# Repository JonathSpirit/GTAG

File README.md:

# GTAG

Copyright (C) 2020 Guillaume Guillet\
Licensed under CERN OHL v.1.2

<table border="0px">
<tr>
<td>
This documentation describes Open Hardware and is licensed under the CERN OHL v. 1.2.
</td>
</tr>
<tr>
<td>
You may redistribute and modify this documentation under the terms of the
CERN OHL v.1.2. (http://ohwr.org/cernohl). This documentation is distributed
WITHOUT ANY EXPRESS OR IMPLIED WARRANTY, INCLUDING OF
MERCHANTABILITY, SATISFACTORY QUALITY AND FITNESS FOR A
PARTICULAR PURPOSE. Please see the CERN OHL v.1.2 for applicable
conditions
</td>
</tr>
</table>

## Description
GTAG is a small adaptation card for the silicon-labs JTAG Debug adapter.
The utility is to not having to place the big 1x05 header connector and not solder any resistance for
small board conception.

Silicon-labs USB-Debug-Adapter : https://www.silabs.com/documents/public/user-guides/8-bit-USB-Debug-Adapter.pdf

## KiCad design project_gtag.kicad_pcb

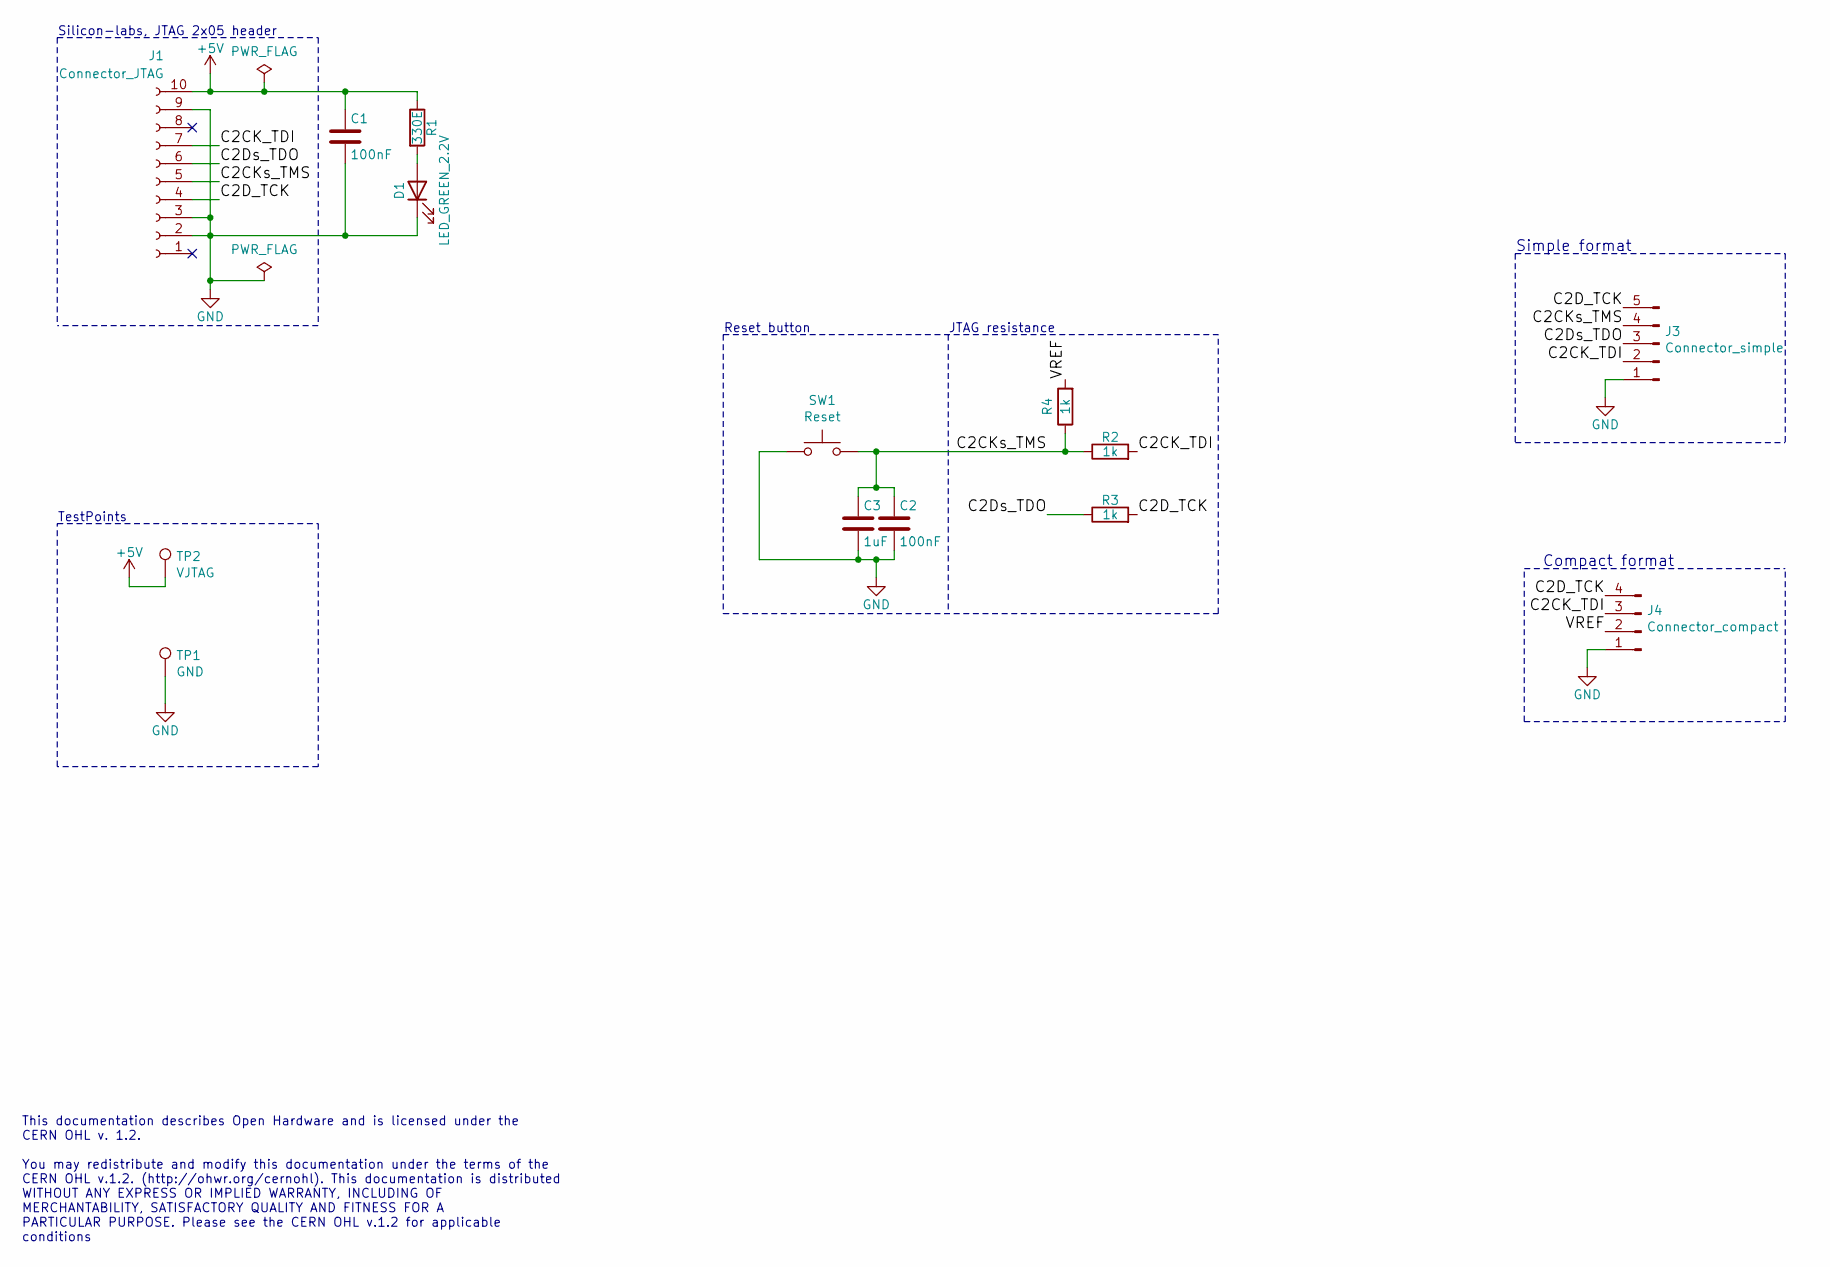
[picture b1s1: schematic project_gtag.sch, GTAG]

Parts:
C1, C2: 100nF; C_1206_3216Metric
C3: 1uF; C_1206_3216Metric
D1: LED_GREEN_2.2V; LED_1206_3216Metric
J1: Connector_JTAG; IDC-Header_2x05_P2.54mm_Horizontal
J3: Connector_simple; PinHeader_1x05_P2.54mm_Horizontal
J4: Connector_compact; PinHeader_1x04_P2.54mm_Horizontal
R1: 330E; R_1206_3216Metric
R2, R3, R4: 1k; R_1206_3216Metric
SW1: Reset; SW_PUSH_6mm
TP1: GND; TestPoint_Loop_D3.50mm_Drill1.4mm_Beaded
TP2: VJTAG; TestPoint_Loop_D3.50mm_Drill1.4mm_Beaded

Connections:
+5V: C1.1, J1.10, R1.1, TP2.1
/C2CK_TDI: J1.7, J3.2, J4.3, R2.2
/C2CKs_TMS: C2.1, C3.1, J1.5, J3.4, R2.1, R4.1, SW1.2
/C2D_TCK: J1.4, J3.5, J4.4, R3.2
/C2Ds_TDO: J1.6, J3.3, R3.1
/VREF: J4.2, R4.2
GND: C1.2, C2.2, C3.2, D1.1 (K), J1.2, J1.3, J1.9, J3.1, J4.1, SW1.1, TP1.1
unnamed: D1.2 (A), R1.2

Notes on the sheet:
Compact format
Simple format
Silicon-labs, JTAG 2x05 header
Reset button
JTAG resistance
TestPoints
This documentation describes Open Hardware and is licensed under the CERN OHL v. 1.2. You may redistribute and modify this documentation under the terms of the CERN OHL v.1.2. (http://ohwr.org/cernohl). This documentation is distributed WITHOUT ANY EXPRESS OR IMPLIED WARRANTY, INCLUDING OF MERCHANT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

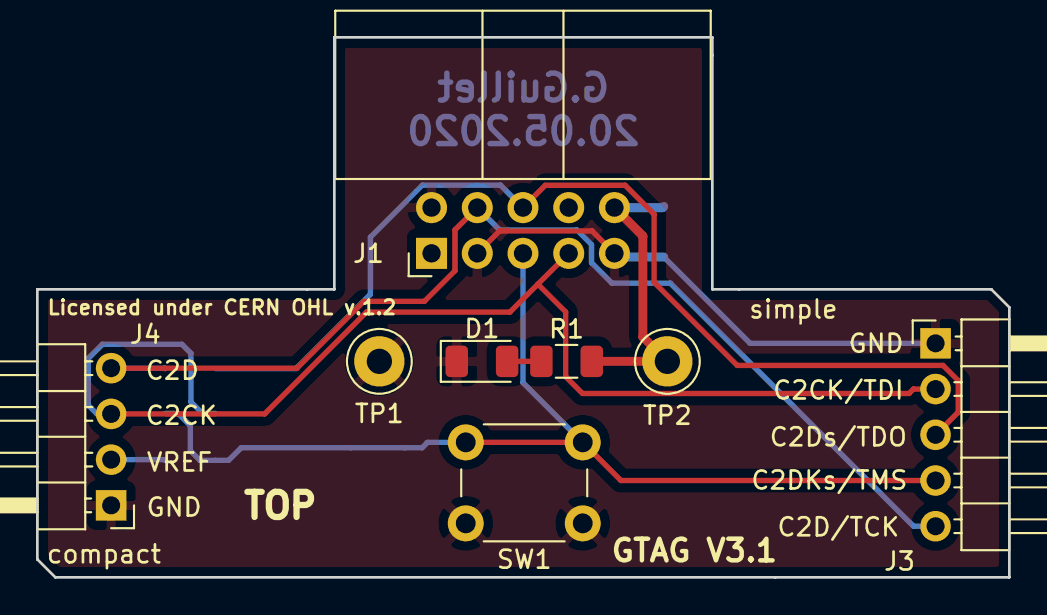
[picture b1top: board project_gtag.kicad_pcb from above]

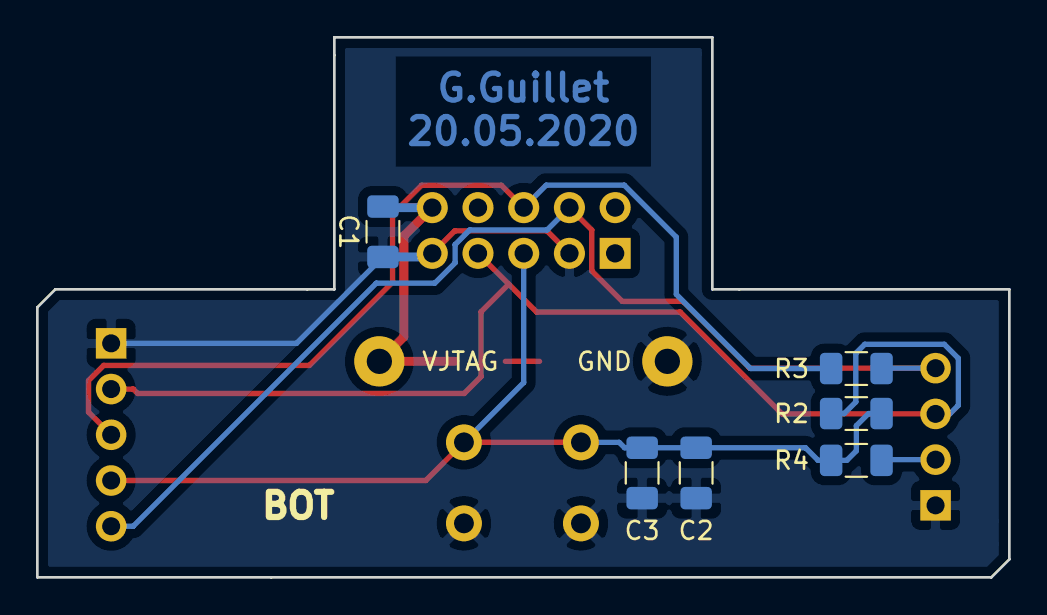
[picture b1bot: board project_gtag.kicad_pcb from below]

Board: 2 copper layers, 54.0 x 30.0 mm, 14 parts (6 on the bottom side), 8 nets.

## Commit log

2020-05-19 Add license, V3.1 and gerbert file
2020-05-20 Add images
2020-05-20 Add representation, docs
2020-05-20 Moving info.txt into docs/info.txt
2020-05-20 Remove old lib refs
